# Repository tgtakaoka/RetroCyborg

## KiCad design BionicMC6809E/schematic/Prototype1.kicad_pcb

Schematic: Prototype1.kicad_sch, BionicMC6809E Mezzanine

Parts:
C1: 0.1u; C_Disc_D3.4mm_W2.1mm_P2.50mm
J1: BionicConnector; DIP-48_W7.62mm
U1: MC6809EP; DIP-40_W15.24mm
U2: 74HCT126; DIP-14_W7.62mm

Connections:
/P10: J1.2 (P10), U1.31 (D0)
/P11: J1.3 (P11), U1.30 (D1)
/P12: J1.4 (P12), U1.29 (D2)
/P13: J1.5 (P13), U1.28 (D3)
/P14: J1.6 (P14), U1.27 (D4)
/P15: J1.7 (P15), U1.26 (D5)
/P16: J1.8 (P16), U1.25 (D6)
/P17: J1.9 (P17), U1.24 (D7)
/P20: J1.47 (P20), U1.8 (A0)
/P21: J1.46 (P21), U1.9 (A1)
/P22: J1.45 (P22), U1.10 (A2)
/P23: J1.44 (P23), U1.11 (A3)
/P24: J1.43 (P24), U1.12 (A4)
/P25: J1.42 (P25), U1.13 (A5)
/P26: J1.41 (P26), U1.14 (A6)
/P27: J1.40 (P27), U1.15 (A7)
/P30: J1.11 (P30), U1.16 (A8)
/P31: J1.12 (P31), U1.17 (A9)
/P32: J1.13 (P32), U1.18 (A10)
/P33: J1.14 (P33), U1.19 (A11)
/P34: J1.15 (P34), U1.20 (A12)
/P35: J1.16 (P35), U1.21 (A13)
/P36: J1.17 (P36), U1.22 (A14)
/P37: J1.18 (P37), U1.23 (A15)
/P40: J1.38 (P40), U1.40 (~HALT)
/P41: J1.37 (P41), U1.32 (R/~W)
/P42: J1.36 (P42), U1.3 (~IRQ)
/P43: J1.35 (P43), U1.2 (~NMI)
/P44: J1.34 (P44), U1.33 (BUSY)
/P45: J1.33 (P45), U1.4 (~FIRQ)
/P46: J1.32 (P46), U2.5 (2A)
/P47: J1.31 (P47), U2.2 (1A)
/P50: J1.20 (P50), U1.36 (AVMA)
/P51: J1.21 (P51), U1.5 (BS)
/P52: J1.22 (P52), U1.38 (LIC)
/P53: J1.23 (P53), U2.9 (3A)
/P54: J1.29 (P54), U1.39 (TSC)
/P55: J1.28 (P55), U1.6 (BA)
GND: C1.2, J1.1 (GND), J1.48 (GND), U1.1 (VSS), U2.7 (GND), U2.12 (4A), U2.13 (4OE)
unnamed: U1.34 (E), U2.6 (2Y)
unnamed: U1.35 (Q), U2.3 (1Y)
unnamed: U1.37 (~RESET), U2.8 (3Y)
VCC: C1.1, J1.24 (VCC), J1.25 (VCC), U1.7 (VCC), U2.1 (1OE), U2.4 (2OE), U2.10 (3OE), U2.14 (VCC)

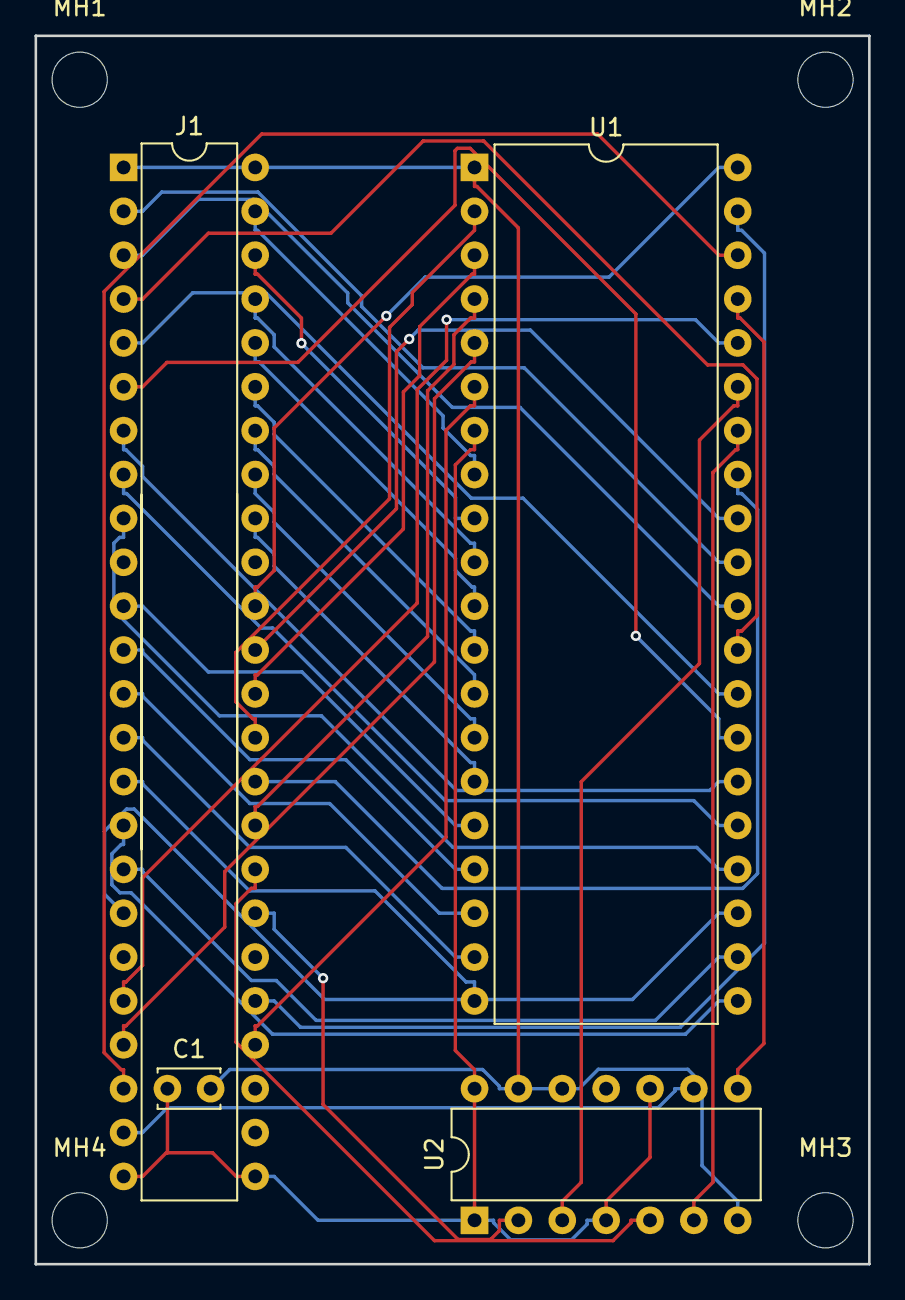
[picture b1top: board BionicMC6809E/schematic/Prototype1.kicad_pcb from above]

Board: 2 copper layers, 48.3 x 71.1 mm, 8 parts (0 on the bottom side), 43 nets.

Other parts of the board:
MH1, MH2, MH3, MH4: MountingHole_3.2mm_M3

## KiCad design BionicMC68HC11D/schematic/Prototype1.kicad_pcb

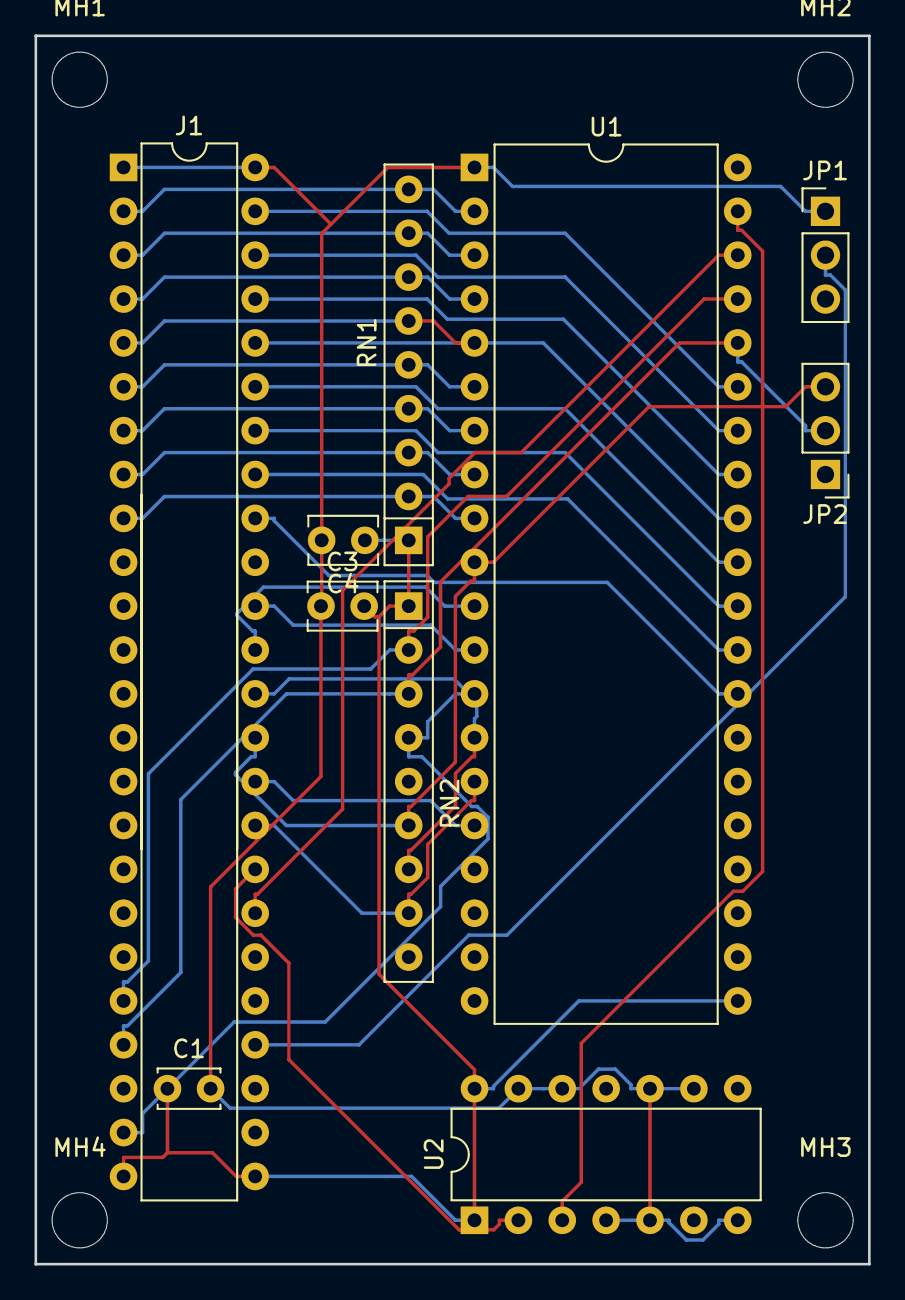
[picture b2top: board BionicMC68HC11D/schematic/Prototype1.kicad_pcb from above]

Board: 2 copper layers, 48.3 x 71.1 mm, 14 parts (0 on the bottom side), 31 nets.

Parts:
C1: 0.1u; C_Disc_D3.4mm_W2.1mm_P2.50mm
C3, C4: 100uF; C_Disc_D3.8mm_W2.6mm_P2.50mm
J1: BionicConnector; DIP-48_W7.62mm
JP1: MC/HD; PinHeader_1x03_P2.54mm_Vertical
JP2: SingleStep; PinHeader_1x03_P2.54mm_Vertical
MH1, MH2, MH3, MH4: MountingHole_3.2mm_M3
RN1: 10k; R_Array_SIP9
RN2: 4.7k; R_Array_SIP9
U1: MC68HC11D0P; DIP-40_W15.24mm
U2: 74HCT126; DIP-14_W7.62mm

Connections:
/P10: J1.2, RN1.9, U1.2
/P11: J1.3, RN1.8, U1.3
/P12: J1.4, RN1.7, U1.4
/P13: J1.5, RN1.6, U1.5
/P14: J1.6, RN1.5, U1.6
/P15: J1.7, RN1.4, U1.7
/P16: J1.8, RN1.3, U1.8
/P17: J1.9, RN1.2, U1.9
/P20: J1.47, U1.35
/P21: J1.46, U1.34
/P22: J1.45, U1.33
/P23: J1.44, U1.32
/P24: J1.43, U1.31
/P25: J1.42, U1.30
/P26: J1.41, U1.29
/P27: J1.40, U1.28
/P40: J1.38, U1.12
/P41: J1.37, U1.11
/P42: J1.36, RN2.7, U1.14
/P43: J1.35, JP2.3, RN2.6, U1.10
/P44: J1.34, U1.16
/P45: J1.33, RN2.8, U1.15
/P46: J1.32, U2.2
/P47: J1.31, U1.38
/P50: J1.20, RN2.2, U1.37
/P51: J1.21, JP2.2, RN2.3, U1.36
/P53: J1.23, RN2.4, U1.13
GND: C1.2, C3.1, C4.2, J1.1, J1.48, JP1.1, U1.1, U2.4, U2.5, U2.7, U2.9, U2.10, U2.12, U2.13
unnamed: J1.28, JP1.2
unnamed: U1.39, U2.3
VCC: C1.1, C3.2, C4.1, J1.24, J1.25, RN1.1, RN2.1, U1.21, U2.1, U2.14

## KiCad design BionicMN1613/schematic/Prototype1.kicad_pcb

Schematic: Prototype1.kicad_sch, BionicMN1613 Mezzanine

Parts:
C1: 0.1u; C_Disc_D3.4mm_W2.1mm_P2.50mm
J1: BionicConnector; DIP-48_W7.62mm
U1: MN1613A; DIP-42_W15.24mm
U2: 74HCT126; DIP-14_W7.62mm

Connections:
/P10: J1.2 (P10), U1.20 (BS15)
/P11: J1.3 (P11), U1.19 (BS14)
/P12: J1.4 (P12), U1.18 (BS13)
/P13: J1.5 (P13), U1.17 (BS12)
/P14: J1.6 (P14), U1.16 (BS11)
/P15: J1.7 (P15), U1.15 (BS10)
/P16: J1.8 (P16), U1.14 (BS09)
/P17: J1.9 (P17), U1.13 (BS08)
/P20: J1.47 (P20), U1.12 (BS07)
/P21: J1.46 (P21), U1.11 (BS06)
/P22: J1.45 (P22), U1.10 (BS05)
/P23: J1.44 (P23), U1.9 (BS04)
/P24: J1.43 (P24), U1.8 (BS03)
/P25: J1.42 (P25), U1.7 (BS02)
/P26: J1.41 (P26), U1.6 (BS01)
/P27: J1.40 (P27), U1.5 (BS00)
/P30: J1.11 (P30), U1.4 (EA3/CSTP)
/P31: J1.12 (P31), U1.3 (EA2/FSYC)
/P32: J1.13 (P32), U1.1 (EA1)
/P33: J1.14 (P33), U1.42 (EA0)
/P34: J1.15 (P34), U1.34 (IOP)
/P35: J1.16 (P35), U1.29 (~IRQ2)
/P36: J1.17 (P36), U1.28 (~IRQ1)
/P37: J1.18 (P37), U1.27 (~IRQ0)
/P40: J1.38 (P40), U1.33 (~BREQ)
/P41: J1.37 (P41), U1.31 (BSAV)
/P42: J1.36 (P42), U1.36 (~DTST)
/P43: J1.35 (P43), U1.32 (~DTAK)
/P44: J1.34 (P44), U1.37 (ADSD)
/P45: J1.33 (P45), U1.35 (WRT)
/P46: J1.32 (P46), U2.2 (1A)
/P47: J1.31 (P47), U1.38 (SYNC)
/P50: J1.20 (P50), U1.24 (~CSRQ/~RUN)
/P51: J1.21 (P51), U1.26 (~HLT)
/P52: J1.22 (P52), U1.25 (~STRT)
/P53: J1.23 (P53), U1.30 (~RST)
/P55: J1.28 (P55), U1.2 (~OE)
GND: C1.2, J1.1 (GND), J1.48 (GND), U1.21 (VSS), U2.4 (2OE), U2.5 (2A), U2.7 (GND), U2.9 (3A), U2.10 (3OE), U2.12 (4A), U2.13 (4OE)
unnamed: U1.39 (X2), U2.3 (1Y)
VCC: C1.1, J1.24 (VCC), J1.25 (VCC), U1.41 (VDD), U2.1 (1OE), U2.14 (VCC)

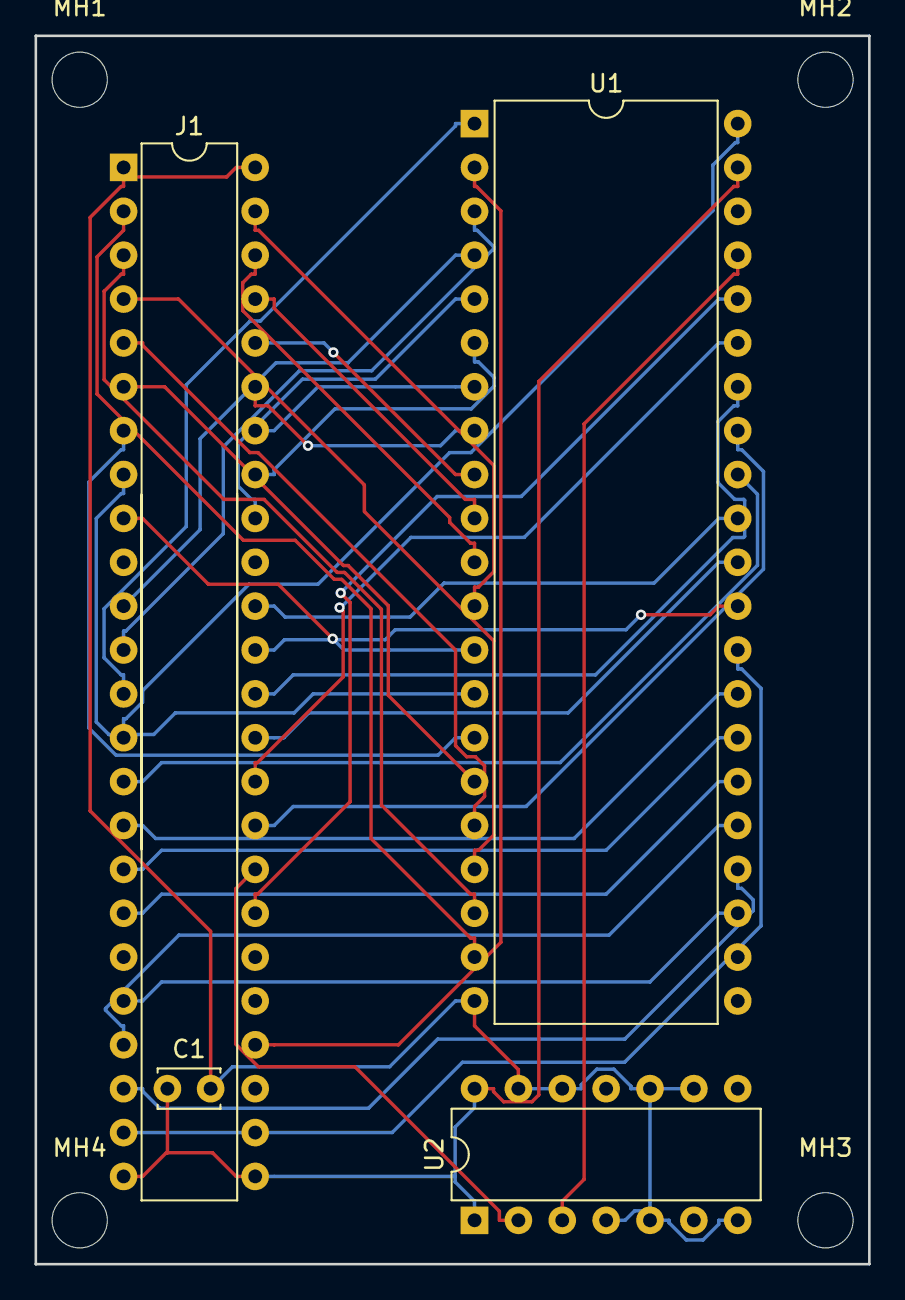
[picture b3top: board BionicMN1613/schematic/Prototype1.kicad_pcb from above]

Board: 2 copper layers, 48.3 x 71.1 mm, 8 parts (0 on the bottom side), 40 nets.

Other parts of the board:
MH1, MH2, MH3, MH4: MountingHole_3.2mm_M3

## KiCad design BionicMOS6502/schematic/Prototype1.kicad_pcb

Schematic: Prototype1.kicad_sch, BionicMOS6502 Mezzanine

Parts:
C1, C2, C3: 0.1u; C_Disc_D3.4mm_W2.1mm_P2.50mm
J1: BionicConnector; DIP-48_W7.62mm
R1: 10k; R_Axial_DIN0204_L3.6mm_D1.6mm_P5.08mm_Horizontal
RN1: 10k; R_Array_SIP9
RN2: 10k; R_Array_SIP5
U1: W65C816S; DIP-40_W15.24mm
U2: 74HC126; DIP-14_W7.62mm

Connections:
/P10: J1.2 (P10), RN1.9 (R8), U1.33 (D0)
/P11: J1.3 (P11), RN1.8 (R7), U1.32 (D1)
/P12: J1.4 (P12), RN1.7 (R6), U1.31 (D2)
/P13: J1.5 (P13), RN1.6 (R5), U1.30 (D3)
/P14: J1.6 (P14), RN1.5 (R4), U1.29 (D4)
/P15: J1.7 (P15), RN1.4 (R3), U1.28 (D5)
/P16: J1.8 (P16), RN1.3 (R2), U1.27 (D6)
/P17: J1.9 (P17), RN1.2 (R1), U1.26 (D7)
/P20: J1.47 (P20), U1.9 (A0)
/P21: J1.46 (P21), U1.10 (A1)
/P22: J1.45 (P22), U1.11 (A2)
/P23: J1.44 (P23), U1.12 (A3)
/P24: J1.43 (P24), U1.13 (A4)
/P25: J1.42 (P25), U1.14 (A5)
/P26: J1.41 (P26), U1.15 (A6)
/P27: J1.40 (P27), U1.16 (A7)
/P30: J1.11 (P30), U1.17 (A8)
/P31: J1.12 (P31), U1.18 (A9)
/P32: J1.13 (P32), U1.19 (A10)
/P33: J1.14 (P33), U1.20 (A11)
/P34: J1.15 (P34), U1.22 (A12)
/P35: J1.16 (P35), U1.23 (A13)
/P36: J1.17 (P36), U1.24 (A14)
/P37: J1.18 (P37), U1.25 (A15)
/P40: J1.38 (P40), U1.35 (E)
/P41: J1.37 (P41), U1.34 (R/~W)
/P42: J1.36 (P42), RN2.3 (R2), U1.4 (~IRQ)
/P43: J1.35 (P43), RN2.2 (R1), U1.6 (~NMI)
/P44: J1.34 (P44), U1.5 (#ML)
/P45: J1.33 (P45), U1.38 (MX)
/P46: J1.32 (P46), U2.2 (1A)
/P47: J1.31 (P47), U1.39 (VDA)
/P50: J1.20 (P50), RN2.4 (R3), U1.3 (~ABORT)
/P51: J1.21 (P51), U1.7 (VPA)
/P52: J1.22 (P52), RN2.5 (R4), U1.2 (RDY)
/P53: J1.23 (P53), R1.2, U2.9 (3A)
/P54: J1.29 (P54), U2.5 (2A)
/P55: J1.28 (P55), U1.1 (#VP)
GND: C1.2, C2.2, C3.2, J1.1 (GND), J1.48 (GND), U1.21 (VSS), U2.7 (GND), U2.12 (4A), U2.13 (4OE)
unnamed: U1.36 (BE), U2.6 (2Y)
unnamed: U1.37 (PHI2I), U2.3 (1Y)
unnamed: U1.40 (~RES), U2.8 (3Y)
VCC: C1.1, C2.1, C3.1, J1.24 (VCC), J1.25 (VCC), R1.1, RN1.1 (common), RN2.1 (common), U1.8 (VCC), U2.1 (1OE), U2.4 (2OE), U2.10 (3OE), U2.14 (VCC)

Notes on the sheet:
N.C. :36
PHI0 :37
35: N.C.
MOS6502
5: N.C.
W65C02S
7: SYNC
PHI1O :3
39: PHI2O
1: VSS
5: ~{ML}
1: #VP
38: ~{SO}

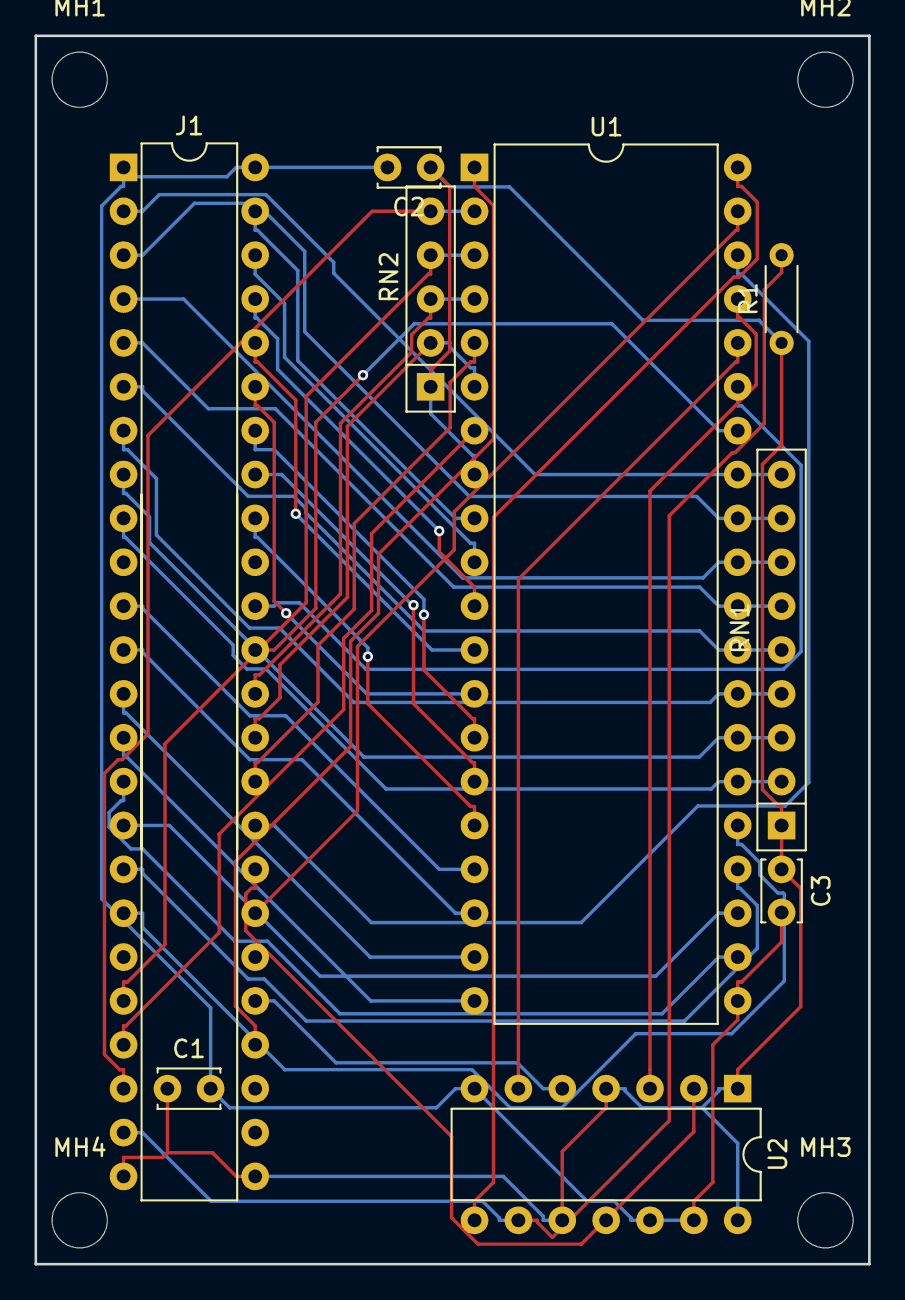
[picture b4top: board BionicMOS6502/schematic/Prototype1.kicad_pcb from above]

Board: 2 copper layers, 48.3 x 71.1 mm, 13 parts (0 on the bottom side), 43 nets.

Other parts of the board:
MH1, MH2, MH3, MH4: MountingHole_3.2mm_M3

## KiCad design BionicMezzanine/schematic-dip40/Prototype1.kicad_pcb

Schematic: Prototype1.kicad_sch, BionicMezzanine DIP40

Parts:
C1: 0.1uF; C_Disc_D3.0mm_W1.6mm_P2.50mm
J1: BionicConnector; DIP-48_W10.16mm
J2, J3: Conn_02x25_Odd_Even; PinSocket_2x25_P2.54mm_Vertical
J4: ZIF_Socket_40pin; Aries_ZIF_socket_DIP-40-pin
J5, J6: Conn_02x20_Odd_Even; PinSocket_2x20_P2.54mm_Vertical
J7, J8: Conn_02x10_Odd_Even; PinSocket_2x10_P2.54mm_Vertical
U1: 74HCT541; DIP-20_W7.62mm

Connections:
/E0: J1.10 (E0), J2.19, J2.20
/E1: J1.39 (E1), J3.19, J3.20
/E2: J1.19 (E2), J2.37, J2.38
/E3: J1.30 (E3), J3.37, J3.38
/P10: J1.2 (P10), J2.3, J2.4
/P11: J1.3 (P11), J2.5, J2.6
/P12: J1.4 (P12), J2.7, J2.8
/P13: J1.5 (P13), J2.9, J2.10
/P14: J1.6 (P14), J2.11, J2.12
/P15: J1.7 (P15), J2.13, J2.14
/P16: J1.8 (P16), J2.15, J2.16
/P17: J1.9 (P17), J2.17, J2.18
/P20: J1.47 (P30), J3.3, J3.4
/P21: J1.46 (P31), J3.5, J3.6
/P22: J1.45 (P32), J3.7, J3.8
/P23: J1.44 (P33), J3.9, J3.10
/P24: J1.43 (P34), J3.11, J3.12
/P25: J1.42 (P35), J3.13, J3.14
/P26: J1.41 (P36), J3.15, J3.16
/P27: J1.40 (P37), J3.17, J3.18
/P30: J1.11 (P20), J2.21, J2.22
/P31: J1.12 (P21), J2.23, J2.24
/P32: J1.13 (P22), J2.25, J2.26
/P33: J1.14 (P23), J2.27, J2.28
/P34: J1.15 (P24), J2.29, J2.30
/P35: J1.16 (P25), J2.31, J2.32
/P36: J1.17 (P26), J2.33, J2.34
/P37: J1.18 (P27), J2.35, J2.36
/P40: J1.38 (P40), J3.21, J3.22
/P41: J1.37 (P41), J3.23, J3.24
/P42: J1.36 (P42), J3.25, J3.26
/P43: J1.35 (P43), J3.27, J3.28
/P44: J1.34 (P44), J3.29, J3.30
/P45: J1.33 (P45), J3.31, J3.32
/P46: J1.32 (P46), J3.33, J3.34
/P47: J1.31 (P47), J3.35, J3.36
/P50: J1.20 (P50), J2.39, J2.40
/P51: J1.21 (P51), J2.41, J2.42
/P52: J1.22 (P52), J2.43, J2.44
/P53: J1.23 (P53), J2.45, J2.46
/P54: J1.29 (P54), J3.39, J3.40
/P55: J1.28 (P55), J3.41, J3.42
/P56: J1.27 (P56), J3.43, J3.44
/P57: J1.26 (P57), J3.45, J3.46
GND: C1.2, J1.1 (GND), J1.48 (GND), J2.1, J2.2, J3.1, J3.2, J7.19, J7.20, J8.19, J8.20, U1.1 (G1), U1.10 (GND), U1.19 (G2)
unnamed: J2.49, J2.50, J3.49, J3.50
unnamed: J4.1 (T1), J5.1, J5.2
unnamed: J4.2 (T2), J5.3, J5.4
unnamed: J4.3 (T3), J5.5, J5.6
unnamed: J4.4 (T4), J5.7, J5.8
unnamed: J4.5 (T5), J5.9, J5.10
unnamed: J4.6 (T6), J5.11, J5.12
unnamed: J4.7 (T7), J5.13, J5.14
unnamed: J4.8 (T8), J5.15, J5.16
unnamed: J4.9 (T9), J5.17, J5.18
unnamed: J4.10 (T10), J5.19, J5.20
unnamed: J4.11 (T11), J5.21, J5.22
unnamed: J4.12 (T12), J5.23, J5.24
unnamed: J4.13 (T13), J5.25, J5.26
unnamed: J4.14 (T14), J5.27, J5.28
unnamed: J4.15 (T15), J5.29, J5.30
unnamed: J4.16 (T16), J5.31, J5.32
unnamed: J4.17 (T17), J5.33, J5.34
unnamed: J4.18 (T18), J5.35, J5.36
unnamed: J4.19 (T19), J5.37, J5.38
unnamed: J4.20 (T20), J5.39, J5.40
unnamed: J4.21 (T21), J6.39, J6.40
unnamed: J4.22 (T22), J6.37, J6.38
unnamed: J4.23 (T23), J6.35, J6.36
unnamed: J4.24 (T24), J6.33, J6.34
unnamed: J4.25 (T25), J6.31, J6.32
unnamed: J4.26 (T26), J6.29, J6.30
unnamed: J4.27 (T27), J6.27, J6.28
unnamed: J4.28 (T28), J6.25, J6.26
unnamed: J4.29 (T29), J6.23, J6.24
unnamed: J4.30 (T30), J6.21, J6.22
unnamed: J4.31 (T31), J6.19, J6.20
unnamed: J4.32 (T32), J6.17, J6.18
unnamed: J4.33 (T33), J6.15, J6.16
unnamed: J4.34 (T34), J6.13, J6.14
unnamed: J4.35 (T35), J6.11, J6.12
unnamed: J4.36 (T36), J6.9, J6.10
unnamed: J4.37 (T37), J6.7, J6.8
unnamed: J4.38 (T38), J6.5, J6.6
unnamed: J4.39 (T39), J6.3, J6.4
unnamed: J4.40 (T40), J6.1, J6.2
unnamed: J7.3, J7.4, U1.2 (A0)
unnamed: J7.5, J7.6, U1.3 (A1)
unnamed: J7.7, J7.8, U1.4 (A2)
unnamed: J7.9, J7.10, U1.5 (A3)
unnamed: J7.11, J7.12, U1.6 (A4)
unnamed: J7.13, J7.14, U1.7 (A5)
unnamed: J7.15, J7.16, U1.8 (A6)
unnamed: J7.17, J7.18, U1.9 (A7)
unnamed: J8.3, J8.4, U1.18 (Y0)
unnamed: J8.5, J8.6, U1.17 (Y1)
unnamed: J8.7, J8.8, U1.16 (Y2)
unnamed: J8.9, J8.10, U1.15 (Y3)
unnamed: J8.11, J8.12, U1.14 (Y4)
unnamed: J8.13, J8.14, U1.13 (Y5)
unnamed: J8.15, J8.16, U1.12 (Y6)
unnamed: J8.17, J8.18, U1.11 (Y7)
VCC: C1.1, J1.24 (VCC), J1.25 (VCC), J2.47, J2.48, J3.47, J3.48, J7.1, J7.2, J8.1, J8.2, U1.20 (VCC)

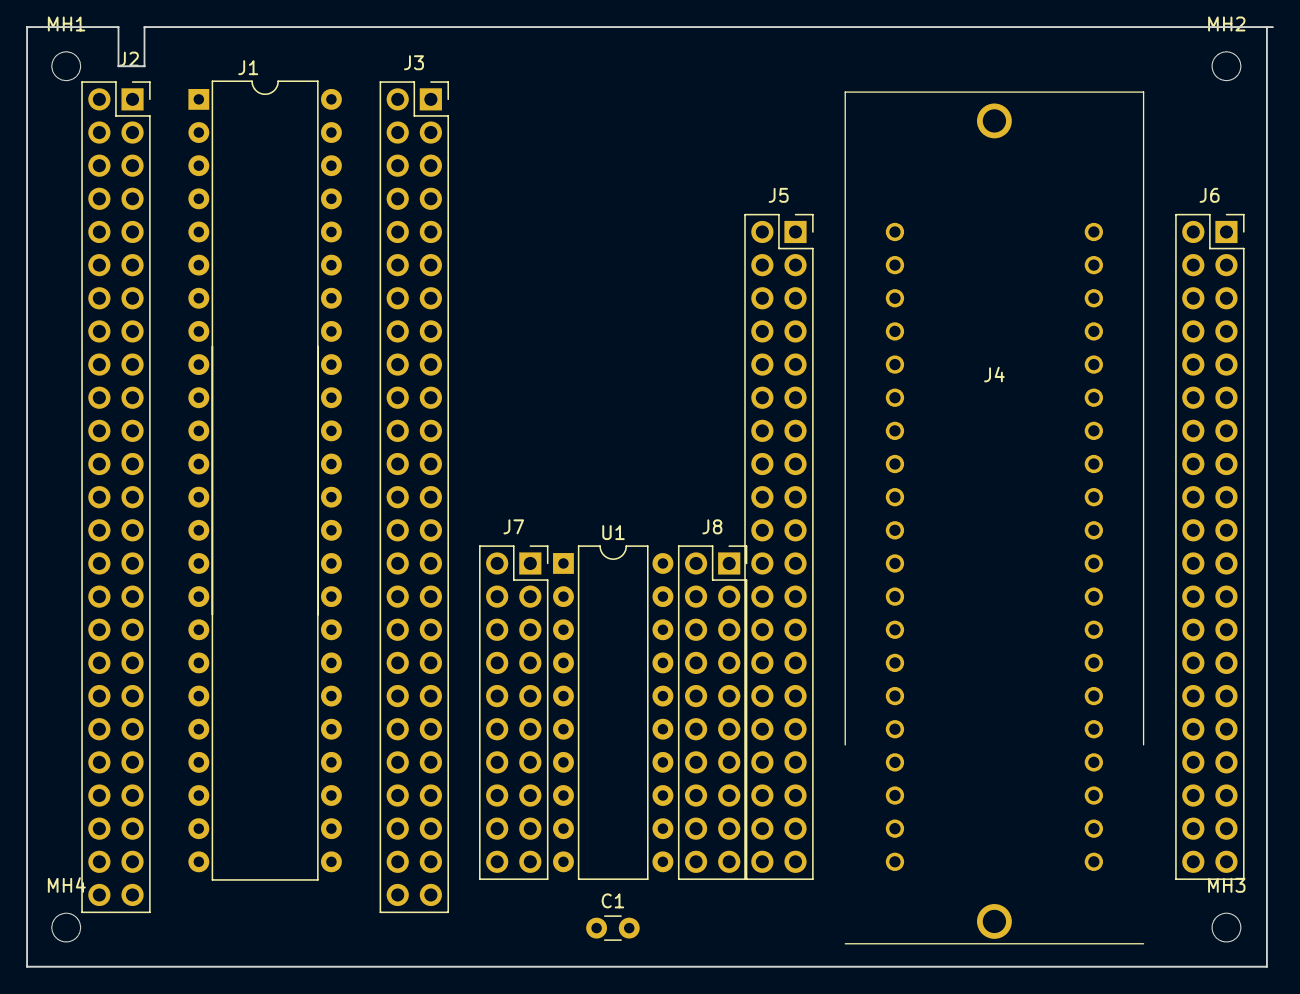
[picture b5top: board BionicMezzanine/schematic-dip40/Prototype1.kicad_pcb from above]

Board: 2 copper layers, 95.5 x 72.0 mm, 14 parts (0 on the bottom side), 103 nets, no tracks yet.

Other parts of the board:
MH1, MH2, MH3, MH4: MountingHole_2.2mm_M2

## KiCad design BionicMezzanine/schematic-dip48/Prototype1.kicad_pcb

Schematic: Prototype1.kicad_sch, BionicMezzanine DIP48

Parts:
C1, C2, C3, C4, C5: 0.1uF; C_Disc_D3.0mm_W1.6mm_P2.50mm
J1: BionicConnector; DIP-48_W10.16mm
J2, J3, J5, J6: Conn_01x24; PinSocket_1x24_P2.54mm_Vertical
J4: ZIF_Socket_48pin; Aries_ZIF_socket_DIP-48-pin
J7, J8: Conn_02x07_Odd_Even; PinSocket_2x07_P2.54mm_Vertical
J9, J10, J11: Conn_01x10; PinSocket_1x10_P2.54mm_Vertical
U1: 74LS126; DIP-14_W7.62mm
U2, U3, U4: 74HCT573; DIP-20_W7.62mm
U5: 74HCT139; DIP-16_W7.62mm

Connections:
/E0: J1.10 (E0), J2.10
/E1: J1.39 (E1), J3.10
/E2: J1.19 (E2), J2.19
/E3: J1.30 (E3), J3.19
/P10: J1.2 (P10), J2.2
/P11: J1.3 (P11), J2.3
/P12: J1.4 (P12), J2.4
/P13: J1.5 (P13), J2.5
/P14: J1.6 (P14), J2.6
/P15: J1.7 (P15), J2.7
/P16: J1.8 (P16), J2.8
/P17: J1.9 (P17), J2.9
/P20: J1.11 (P20), J2.11, U2.18 (1Q), U3.18 (1Q), U4.18 (1Q)
/P21: J1.12 (P21), J2.12, U2.17 (2Q), U3.17 (2Q), U4.17 (2Q)
/P22: J1.13 (P22), J2.13, U2.16 (3Q), U3.16 (3Q), U4.16 (3Q)
/P23: J1.14 (P23), J2.14, U2.15 (4Q), U3.15 (4Q), U4.15 (4Q)
/P24: J1.15 (P24), J2.15, U2.14 (5Q), U3.14 (5Q), U4.14 (5Q)
/P25: J1.16 (P25), J2.16, U2.13 (6Q), U3.13 (6Q), U4.13 (6Q)
/P26: J1.17 (P26), J2.17, U2.12 (7Q), U3.12 (7Q), U4.12 (7Q)
/P30: J1.47 (P30), J3.2
/P31: J1.46 (P31), J3.3
/P32: J1.45 (P32), J3.4
/P33: J1.44 (P33), J3.5
/P34: J1.43 (P34), J3.6
/P35: J1.42 (P35), J3.7
/P36: J1.41 (P36), J3.8
/P37: J1.40 (P37), J3.9
/P40: J1.38 (P40), J3.11
/P41: J1.37 (P41), J3.12
/P42: J1.36 (P42), J3.13
/P43: J1.35 (P43), J3.14
/P44: J1.34 (P44), J3.15
/P45: J1.33 (P45), J3.16
/P46: J1.32 (P46), J3.17
/P47: J1.31 (P47), J3.18
/P50: J1.20 (P50), J2.20
/P51: J1.21 (P51), J2.21
/P52: J1.22 (P52), J2.22
/P53: J1.23 (P53), J2.23
/P54: J1.29 (P54), J3.20
/P55: J1.28 (P55), J3.21
/P56: J1.27 (P56), J3.22
/P57: J1.26 (P57), J3.23
GND: C3.2, C4.2, C5.2, J1.1 (GND), J1.48 (GND), J2.1, J3.1, U2.10 (GND), U3.10 (GND), U4.10 (GND), U5.1 (~E), U5.13 (A1), U5.14 (A0), U5.15 (~E)
unnamed: C1.2, C2.2, J7.13, J7.14, U1.7 (GND), U5.8 (GND)
unnamed: J4.1 (T1), J5.1
unnamed: J4.2 (T2), J5.2
unnamed: J4.3 (T3), J5.3
unnamed: J4.4 (T4), J5.4
unnamed: J4.5 (T5), J5.5
unnamed: J4.6 (T6), J5.6
unnamed: J4.7 (T7), J5.7
unnamed: J4.8 (T8), J5.8
unnamed: J4.9 (T9), J5.9
unnamed: J4.10 (T10), J5.10
unnamed: J4.11 (T11), J5.11
unnamed: J4.12 (T12), J5.12
unnamed: J4.13 (T13), J5.13
unnamed: J4.14 (T14), J5.14
unnamed: J4.15 (T15), J5.15
unnamed: J4.16 (T16), J5.16
unnamed: J4.17 (T17), J5.17
unnamed: J4.18 (T18), J5.18
unnamed: J4.19 (T19), J5.19
unnamed: J4.20 (T20), J5.20
unnamed: J4.21 (T21), J5.21
unnamed: J4.22 (T22), J5.22
unnamed: J4.23 (T23), J5.23
unnamed: J4.24 (T24), J5.24
unnamed: J4.25 (T25), J6.24
unnamed: J4.26 (T26), J6.23
unnamed: J4.27 (T27), J6.22
unnamed: J4.28 (T28), J6.21
unnamed: J4.29 (T29), J6.20
unnamed: J4.30 (T30), J6.19
unnamed: J4.31 (T31), J6.18
unnamed: J4.32 (T32), J6.17
unnamed: J4.33 (T33), J6.16
unnamed: J4.34 (T34), J6.15
unnamed: J4.35 (T35), J6.14
unnamed: J4.36 (T36), J6.13
unnamed: J4.37 (T37), J6.12
unnamed: J4.38 (T38), J6.11
unnamed: J4.39 (T39), J6.10
unnamed: J4.40 (T40), J6.9
unnamed: J4.41 (T41), J6.8
unnamed: J4.42 (T42), J6.7
unnamed: J4.43 (T43), J6.6
unnamed: J4.44 (T44), J6.5
unnamed: J4.45 (T45), J6.4
unnamed: J4.46 (T46), J6.3
unnamed: J4.47 (T47), J6.2
unnamed: J4.48 (T48), J6.1
unnamed: J7.1, J7.2, U1.1 (1OE)
unnamed: J7.3, J7.4, U1.2 (1A)
unnamed: J7.5, J7.6, U1.3 (1Y)
unnamed: J7.7, J7.8, U1.4 (2OE)
unnamed: J7.9, J7.10, U1.5 (2A)
unnamed: J7.11, J7.12, U1.6 (2Y)
unnamed: J9.1, U2.2 (1D)
unnamed: J9.2, U2.3 (2D)
unnamed: J9.3, U2.4 (3D)
unnamed: J9.4, U2.5 (4D)
unnamed: J9.5, U2.6 (5D)
unnamed: J9.6, U2.7 (6D)
unnamed: J9.7, U2.8 (7D)
unnamed: J9.8, U2.9 (8D)
unnamed: J9.10, U5.2 (A0)
unnamed: J10.1, U3.2 (1D)
unnamed: J10.2, U3.3 (2D)
unnamed: J10.3, U3.4 (3D)
unnamed: J10.4, U3.5 (4D)
unnamed: J10.5, U3.6 (5D)
unnamed: J10.6, U3.7 (6D)
unnamed: J10.7, U3.8 (7D)
unnamed: J10.8, U3.9 (8D)
unnamed: J10.10, U5.3 (A1)
unnamed: J11.1, U4.2 (1D)
unnamed: J11.2, U4.3 (2D)
unnamed: J11.3, U4.4 (3D)
unnamed: J11.4, U4.5 (4D)
unnamed: J11.5, U4.6 (5D)
unnamed: J11.6, U4.7 (6D)
unnamed: J11.7, U4.8 (7D)
unnamed: J11.8, U4.9 (8D)
unnamed: U2.1 (~OE), U5.4 (~Y0)
unnamed: U3.1 (~OE), U5.5 (~Y1)
unnamed: U4.1 (~OE), U5.6 (~Y2)
VCC: C1.1, C2.1, C3.1, C4.1, C5.1, J1.24 (VCC), J1.25 (VCC), J2.24, J3.24, J8.2, J8.3, J8.4, J8.5, J8.6, J8.7, J8.8, J8.9, J8.10, J8.11, J8.12, J8.13, J8.14, U1.8 (3Y), U1.9 (3A), U1.10 (3OE), U1.11 (4Y), U1.12 (4A), U1.13 (4OE), U1.14 (VCC), U2.20 (VCC), U3.20 (VCC), U4.20 (VCC), U5.16 (VCC)

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
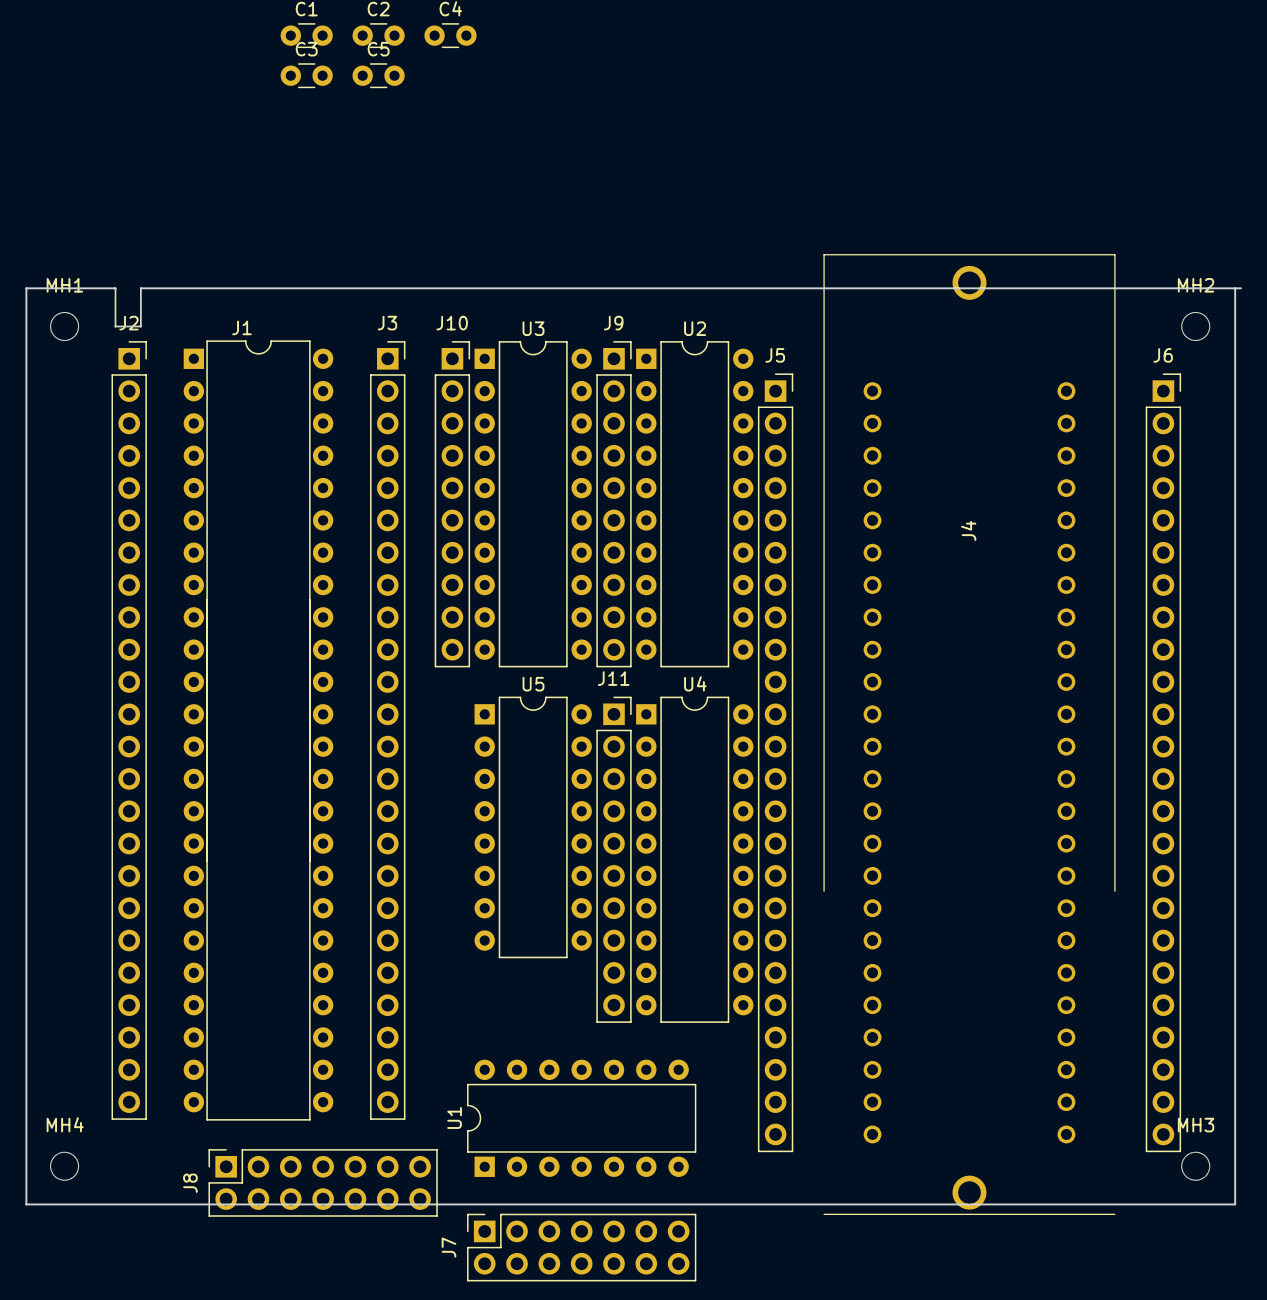
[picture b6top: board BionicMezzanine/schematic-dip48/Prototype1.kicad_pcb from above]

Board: 2 copper layers, 95.5 x 72.0 mm, 25 parts (0 on the bottom side), 131 nets, no tracks yet.

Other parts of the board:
MH1, MH2, MH3, MH4: MountingHole_2.2mm_M2

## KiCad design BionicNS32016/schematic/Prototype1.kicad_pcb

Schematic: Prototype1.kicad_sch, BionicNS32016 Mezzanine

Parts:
C1, C2, C3, C4: 0.1u; C_Disc_D3.4mm_W2.1mm_P2.50mm
C5: 1000p; C_Disc_D3.4mm_W2.1mm_P2.50mm
C6: 1u; C_Disc_D3.4mm_W2.1mm_P2.50mm
J1: BionicConnector; DIP-48_W7.62mm
U1: NS32016N; DIP-48_W15.24mm
U2: 74HCT126; DIP-14_W7.62mm
U3, U4: 74HCT541; DIP-20_W7.62mm

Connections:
/P10: J1.2 (P10), U1.23 (AD0)
/P11: J1.3 (P11), U1.22 (AD1)
/P12: J1.4 (P12), U1.21 (AD2)
/P13: J1.5 (P13), U1.20 (AD3)
/P14: J1.6 (P14), U1.19 (AD4)
/P15: J1.7 (P15), U1.18 (AD5)
/P16: J1.8 (P16), U1.17 (AD6)
/P17: J1.9 (P17), U1.16 (AD7)
/P20: J1.47 (P20), U1.15 (AD8)
/P21: J1.46 (P21), U1.14 (AD9)
/P22: J1.45 (P22), U1.13 (AD10)
/P23: J1.44 (P23), U1.12 (AD11)
/P24: J1.43 (P24), U1.11 (AD12)
/P25: J1.42 (P25), U1.10 (AD13)
/P26: J1.41 (P26), U1.9 (AD14)
/P27: J1.40 (P27), U1.8 (AD15)
/P30: J1.11 (P30), U3.11 (Y7), U4.18 (Y0)
/P31: J1.12 (P31), U3.12 (Y6), U4.17 (Y1)
/P32: J1.13 (P32), U3.13 (Y5), U4.16 (Y2)
/P33: J1.14 (P33), U3.14 (Y4), U4.15 (Y3)
/P34: J1.15 (P34), U3.15 (Y3), U4.14 (Y4)
/P35: J1.16 (P35), U3.16 (Y2), U4.13 (Y5)
/P36: J1.17 (P36), U3.17 (Y1), U4.12 (Y6)
/P37: J1.18 (P37), U1.30 (~HOLD), U3.18 (Y0), U4.11 (Y7)
/P40: J1.38 (P40)
/P41: J1.37 (P41), U1.33 (~DS)
/P42: J1.36 (P42), U1.46 (~INT)
/P43: J1.35 (P43)
/P44: J1.34 (P44), U1.45 (~NMI)
/P45: J1.33 (P45), U1.37 (~ADS)
/P46: J1.32 (P46), U2.5 (2A)
/P47: J1.31 (P47), U1.39 (~PFS), U2.2 (1A)
/P50: J1.20 (P50), U1.35 (~AT)
/P51: J1.21 (P51), U1.28 (RDY)
/P52: J1.22 (P52), U1.31 (~HLDA)
/P53: J1.23 (P53)
/P54: J1.29 (P54), U4.1 (G1), U4.19 (G2)
/P55: J1.28 (P55), U3.1 (G1), U3.19 (G2)
GND: C1.2, C2.2, C3.2, C4.2, C5.2, C6.2, J1.1 (GND), J1.48 (GND), U1.24 (GNDL), U1.25 (GNDB), U2.7 (GND), U2.9 (3A), U2.10 (3OE), U2.12 (4A), U2.13 (4OE), U3.20 (VCC), U4.10 (GND)
unnamed: C5.1, C6.1, U1.29 (BBG)
unnamed: U1.1 (A22), U3.3 (A1)
unnamed: U1.2 (A21), U3.4 (A2)
unnamed: U1.3 (A20), U3.5 (A3)
unnamed: U1.4 (A19), U3.6 (A4)
unnamed: U1.5 (A18), U3.7 (A5)
unnamed: U1.6 (A17), U3.8 (A6)
unnamed: U1.7 (A16), U3.9 (A7)
unnamed: U1.26 (PHI1), U2.6 (2Y)
unnamed: U1.27 (PHI2), U2.3 (1Y)
unnamed: U1.32 (~HBE), U4.9 (A7)
unnamed: U1.36 (U/~S), U4.6 (A4)
unnamed: U1.38 (~DDIN), U4.8 (A6)
unnamed: U1.40 (ST3), U4.5 (A3)
unnamed: U1.41 (ST2), U4.4 (A2)
unnamed: U1.42 (ST1), U4.3 (A1)
unnamed: U1.43 (ST0), U4.2 (A0)
unnamed: U1.44 (~ILO), U4.7 (A5)
unnamed: U1.47 (A23), U3.2 (A0)
VCC: C1.1, C2.1, C3.1, C4.1, J1.24 (VCC), J1.25 (VCC), U1.48 (VCC), U2.1 (1OE), U2.4 (2OE), U2.14 (VCC), U3.10 (GND), U4.20 (VCC)

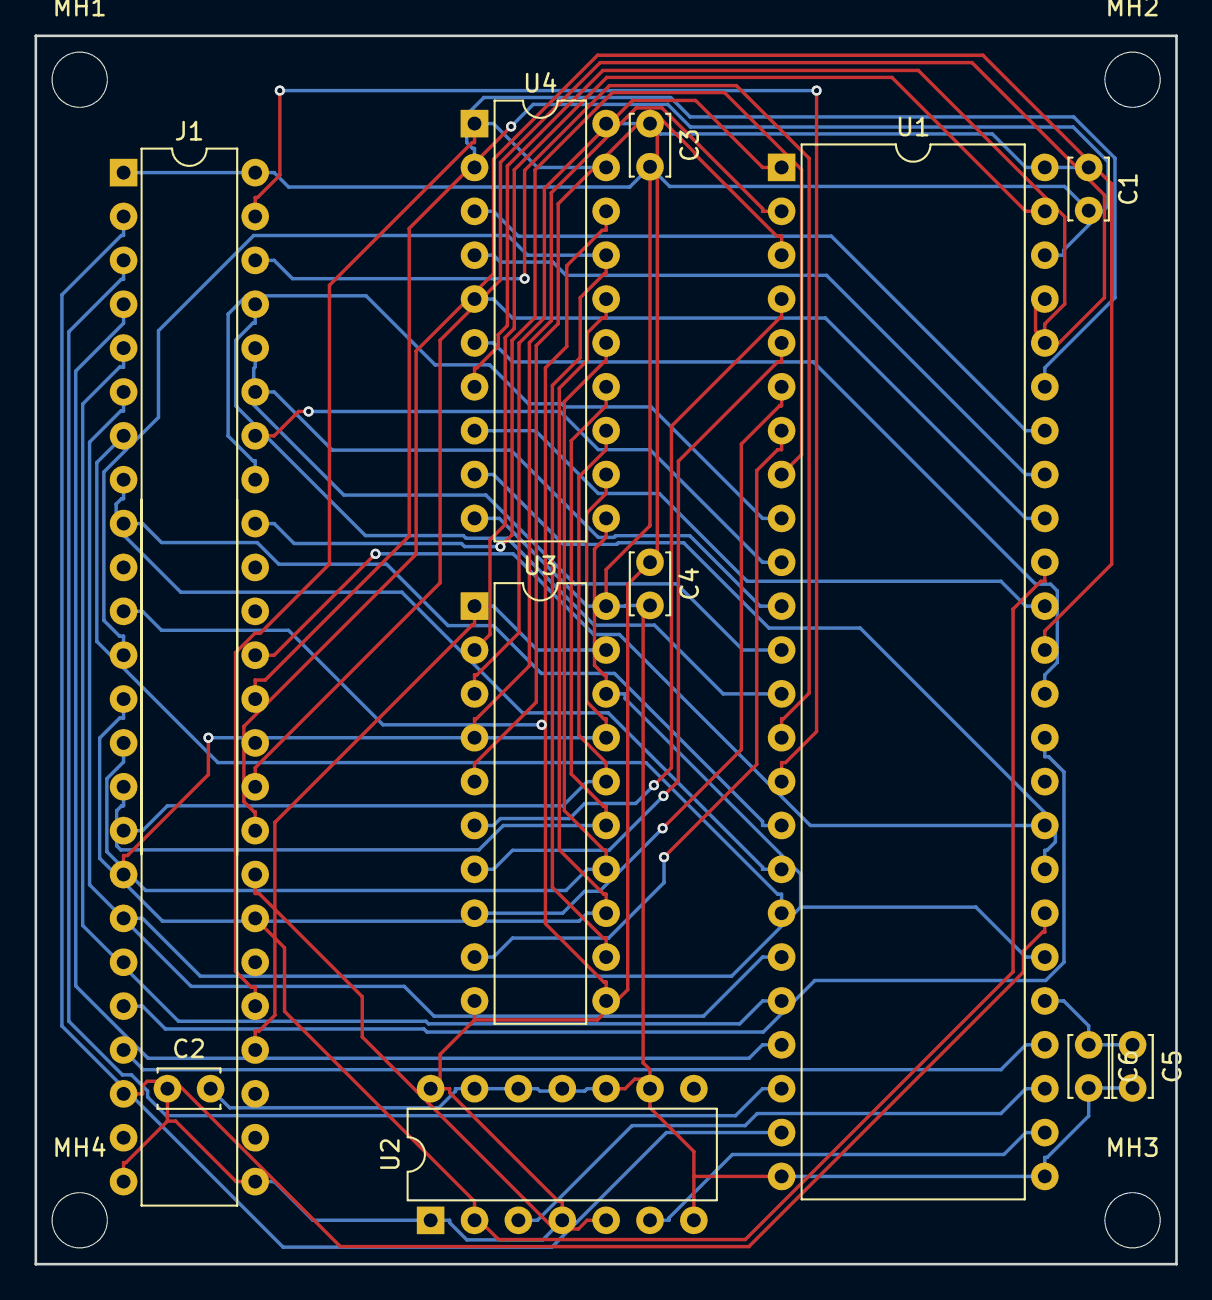
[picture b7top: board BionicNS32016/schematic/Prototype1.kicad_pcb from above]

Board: 2 copper layers, 66.0 x 71.1 mm, 15 parts (0 on the bottom side), 56 nets.

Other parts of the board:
MH1, MH2, MH3, MH4: MountingHole_3.2mm_M3

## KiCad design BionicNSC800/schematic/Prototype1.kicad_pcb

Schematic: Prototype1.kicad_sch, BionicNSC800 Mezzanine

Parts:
C1: 0.1u; C_Disc_D3.4mm_W2.1mm_P2.50mm
J1: BionicConnector; DIP-48_W7.62mm
U1: NSC800N; DIP-40_W15.24mm
U2: 74HCT126; DIP-14_W7.62mm

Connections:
/P10: J1.2 (P10), U1.12 (AD0)
/P11: J1.3 (P11), U1.13 (AD1)
/P12: J1.4 (P12), U1.14 (AD2)
/P13: J1.5 (P13), U1.15 (AD3)
/P14: J1.6 (P14), U1.16 (AD4)
/P15: J1.7 (P15), U1.17 (AD5)
/P16: J1.8 (P16), U1.18 (AD6)
/P17: J1.9 (P17), U1.19 (AD7)
/P20: J1.47 (P20), U1.1 (A8)
/P21: J1.46 (P21), U1.2 (A9)
/P22: J1.45 (P22), U1.3 (A10)
/P23: J1.44 (P23), U1.4 (A11)
/P24: J1.43 (P24), U1.5 (A12)
/P25: J1.42 (P25), U1.6 (A13)
/P26: J1.41 (P26), U1.7 (A14)
/P27: J1.40 (P27), U1.8 (A15)
/P30: J1.11 (P30), U1.22 (~RSTA)
/P31: J1.12 (P31), U1.23 (~RSTB)
/P32: J1.13 (P32), U1.24 (~RSTC)
/P34: J1.15 (P34), U1.29 (S0)
/P35: J1.16 (P35), U1.27 (S1)
/P36: J1.17 (P36), U1.35 (~BACK)
/P37: J1.18 (P37), U1.36 (~BREQ)
/P40: J1.38 (P40), U1.30 (ALE)
/P42: J1.36 (P42), U1.25 (~INTR)
/P43: J1.35 (P43), U1.21 (~NMI)
/P44: J1.34 (P44), U1.39 (~PS)
/P45: J1.33 (P45), U1.28 (~RFSH)
/P46: J1.32 (P46), U2.2 (1A)
/P47: J1.31 (P47), U1.9 (CLK)
/P50: J1.20 (P50), U1.32 (~RD)
/P51: J1.21 (P51), U1.31 (~WR)
/P52: J1.22 (P52), U1.38 (~WAIT)
/P53: J1.23 (P53), U2.5 (2A)
/P54: J1.29 (P54), U1.26 (~INTA)
/P55: J1.28 (P55), U1.34 (IO/~M)
GND: C1.2, J1.1 (GND), J1.48 (GND), U1.20 (VSS), U2.7 (GND), U2.9 (3A), U2.10 (3OE), U2.12 (4A), U2.13 (4OE)
unnamed: U1.11 (XIN), U2.3 (1Y)
unnamed: U1.33 (~RESETIN), U2.6 (2Y)
VCC: C1.1, J1.24 (VCC), J1.25 (VCC), U1.40 (VCC), U2.1 (1OE), U2.4 (2OE), U2.14 (VCC)

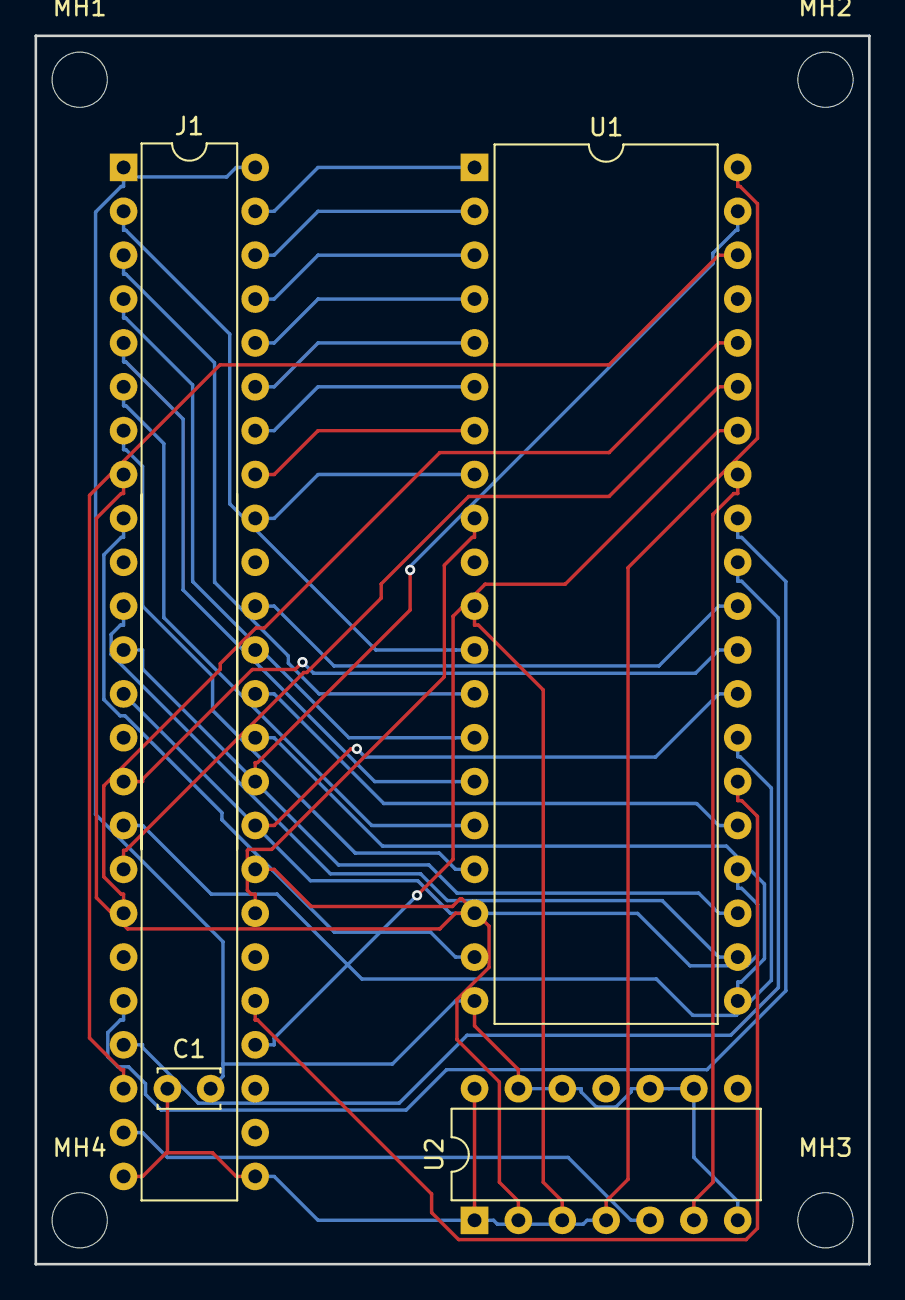
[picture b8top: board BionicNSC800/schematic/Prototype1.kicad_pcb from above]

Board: 2 copper layers, 48.3 x 71.1 mm, 8 parts (0 on the bottom side), 40 nets.

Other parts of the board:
MH1, MH2, MH3, MH4: MountingHole_3.2mm_M3
